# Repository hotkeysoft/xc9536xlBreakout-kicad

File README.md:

# XC9536XL Breakout Board

Rev A October 2019

XC9536XL CPLD Features
============
- 5 ns pin-to-pin logic delays
- System frequency up to 178 MHz
- 36 macrocells with 800 usable gates
- 5V tolerant I/O pins (accept 5 V, 3.3V, and 2.5V signals)
- 3.3V or 2.5V output capability

[datasheet](https://www.xilinx.com/support/documentation/data_sheets/ds058.pdf)

Breakout Board Features
============
- JTAG Programming Header
- 5V->3.3V Voltage Regulator to power XC9536XL
- XC9536XL is 5V tolerant and, with a 3.3V output, is compatible with in 5V TTL projects.

Images
============
|Front                                                 | Back                                              |
|------------------------------------------------------|---------------------------------------------------|
|||

### Schematics (pdf)
- [Complete schematics](./img/schema.pdf)

### PCB Images (svg)
- [Top](./img/pcb-front.svg)
- [Bottom](./img/pcb-back.svg)

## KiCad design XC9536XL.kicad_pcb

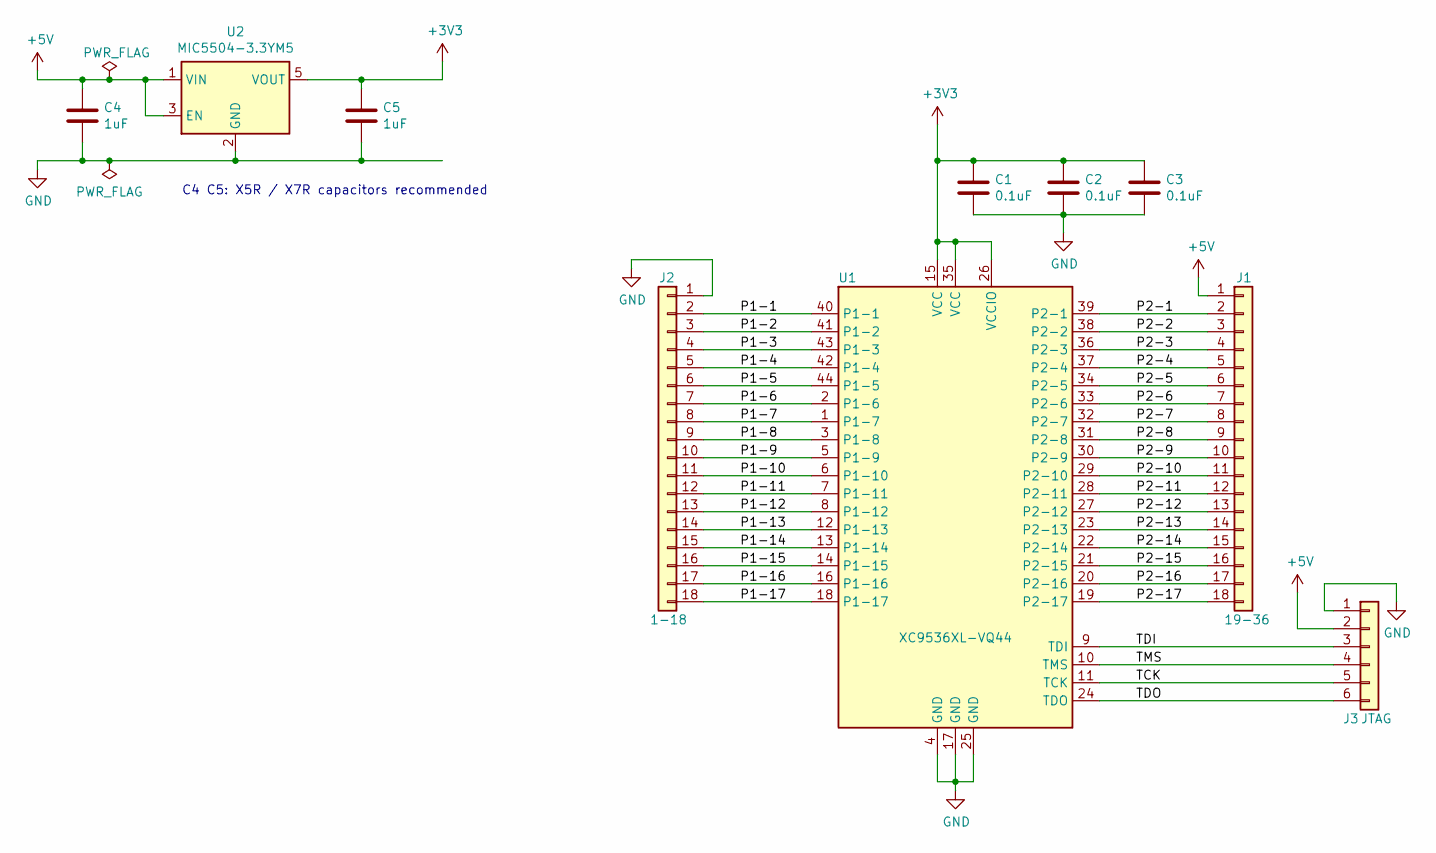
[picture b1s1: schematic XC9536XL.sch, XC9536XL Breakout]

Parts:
C1, C2, C3: 0.1uF; C_0603_1608Metric
C4, C5: 1uF; C_0603_1608Metric
J1: 19-36; PinHeader_1x18_P2.54mm_Vertical
J2: 1-18; PinHeader_1x18_P2.54mm_Vertical
J3: JTAG; PinHeader_1x06_P2.54mm_Vertical
U1: XC9536XL-VQ44; TQFP-44_10x10mm_P0.8mm
U2: MIC5504-3.3YM5; SOT-23-5

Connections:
+3V3: C1.1, C2.1, C3.1, C5.1, U1.15 (VCC), U1.26 (VCCIO), U1.35 (VCC), U2.5 (VOUT)
+5V: C4.1, J1.1, J3.2, U2.1 (VIN), U2.3 (EN)
/P1-1: J2.2, U1.40 (P1-1)
/P1-2: J2.3, U1.41 (P1-2)
/P1-3: J2.4, U1.43 (P1-3)
/P1-4: J2.5, U1.42 (P1-4)
/P1-5: J2.6, U1.44 (P1-5)
/P1-6: J2.7, U1.2 (P1-6)
/P1-7: J2.8, U1.1 (P1-7)
/P1-8: J2.9, U1.3 (P1-8)
/P1-9: J2.10, U1.5 (P1-9)
/P1-10: J2.11, U1.6 (P1-10)
/P1-11: J2.12, U1.7 (P1-11)
/P1-12: J2.13, U1.8 (P1-12)
/P1-13: J2.14, U1.12 (P1-13)
/P1-14: J2.15, U1.13 (P1-14)
/P1-15: J2.16, U1.14 (P1-15)
/P1-16: J2.17, U1.16 (P1-16)
/P1-17: J2.18, U1.18 (P1-17)
/P2-1: J1.2, U1.39 (P2-1)
/P2-2: J1.3, U1.38 (P2-2)
/P2-3: J1.4, U1.36 (P2-3)
/P2-4: J1.5, U1.37 (P2-4)
/P2-5: J1.6, U1.34 (P2-5)
/P2-6: J1.7, U1.33 (P2-6)
/P2-7: J1.8, U1.32 (P2-7)
/P2-8: J1.9, U1.31 (P2-8)
/P2-9: J1.10, U1.30 (P2-9)
/P2-10: J1.11, U1.29 (P2-10)
/P2-11: J1.12, U1.28 (P2-11)
/P2-12: J1.13, U1.27 (P2-12)
/P2-13: J1.14, U1.23 (P2-13)
/P2-14: J1.15, U1.22 (P2-14)
/P2-15: J1.16, U1.21 (P2-15)
/P2-16: J1.17, U1.20 (P2-16)
/P2-17: J1.18, U1.19 (P2-17)
/TCK: J3.5, U1.11 (TCK)
/TDI: J3.3, U1.9 (TDI)
/TDO: J3.6, U1.24 (TDO)
/TMS: J3.4, U1.10 (TMS)
GND: C1.2, C2.2, C3.2, C4.2, C5.2, J2.1, J3.1, U1.4 (GND), U1.17 (GND), U1.25 (GND), U2.2 (GND)

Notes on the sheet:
C4 C5: X5R / X7R capacitors recommended

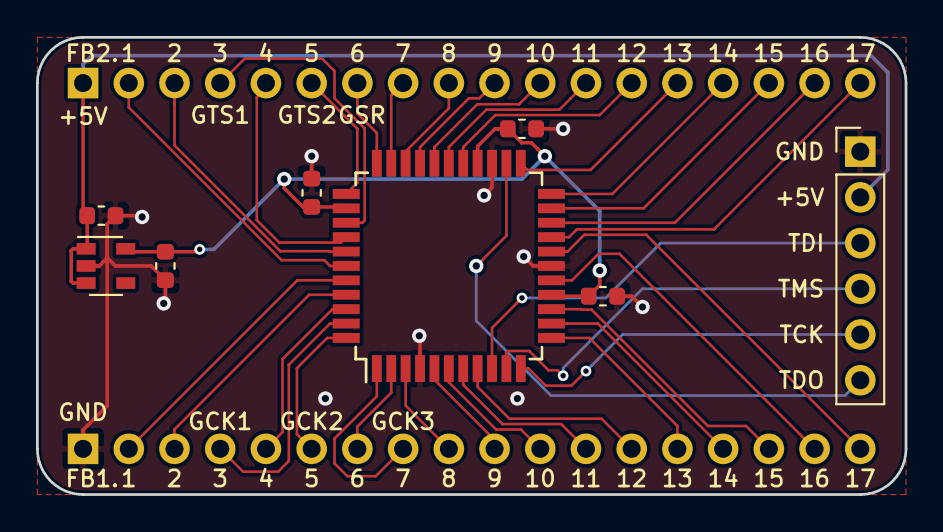
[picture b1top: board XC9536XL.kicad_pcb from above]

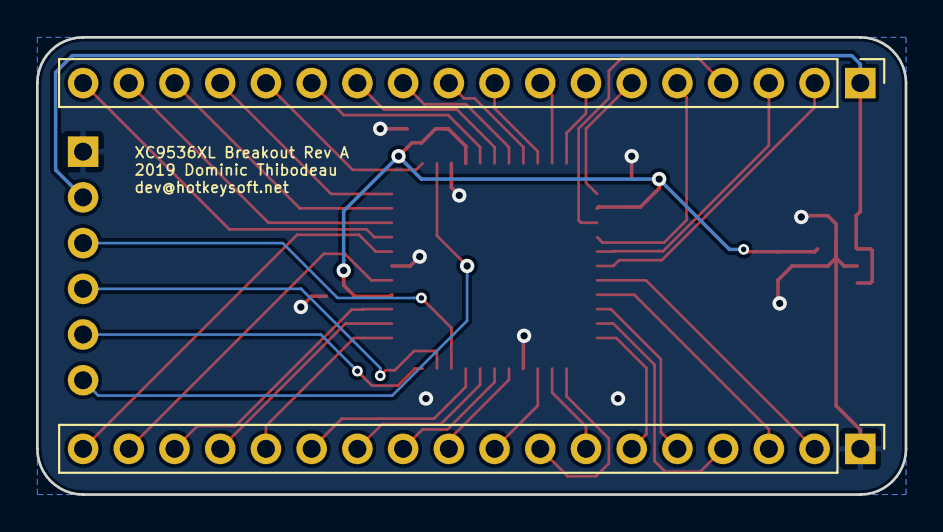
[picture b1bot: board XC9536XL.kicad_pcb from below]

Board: 2 copper layers, 48.3 x 25.4 mm, 10 parts (2 on the bottom side), 41 nets.

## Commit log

2019-10-24 XC9536XL Breakout board
2019-10-24 Added measurements, plots
2019-10-24 lib thing
2020-07-11 Cleanup, add images, README.md and LICENSE
